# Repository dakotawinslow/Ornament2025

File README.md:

# Ornament2025
Repo of associated files for my Cristmas ornament 2025

See https://dakotawinslow.com for more details.

Shield: [![CC BY-SA 4.0][cc-by-sa-shield]][cc-by-sa]

This work is licensed under a
[Creative Commons Attribution-ShareAlike 4.0 International License][cc-by-sa].

[![CC BY-SA 4.0][cc-by-sa-image]][cc-by-sa]

[cc-by-sa]: http://creativecommons.org/licenses/by-sa/4.0/
[cc-by-sa-image]: https://licensebuttons.net/l/by-sa/4.0/88x31.png
[cc-by-sa-shield]: https://img.shields.io/badge/License-CC%20BY--SA%204.0-lightgrey.svg

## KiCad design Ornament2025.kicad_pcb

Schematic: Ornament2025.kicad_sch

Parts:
BT1: 3; BatteryHolder_uxcell_CR2450
C1, C2: 2.2uF; C_0805_2012Metric
D1, D2, D3: GRN; LED_D3.0mm
D4, D5, D6: RED; LED_D3.0mm
Q1, Q2: NPN; TO-92_Inline_Wide
R1, R2, R3: 6.8K; R_0805_2012Metric
R4, R5, R6: 1K; R_0805_2012Metric
R7, R9, R13, R14: 100K; R_0805_2012Metric
R8: 33K; R_0805_2012Metric
R10, R11: 18K; R_0805_2012Metric
R12, R16: 10K; R_0805_2012Metric
R15, R17, R18: 47K; R_0805_2012Metric
SW1, SW2, SW3: SW_SPST; PinHeader_1x03_P2.54mm_Vertical
U1: LMV358; SOIC-8-1EP_3.9x4.9mm_P1.27mm_EP2.29x3mm

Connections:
+1V5: C1.1, C2.1, R7.2, R12.2, R13.2, R16.1
+3V0: R1.1, R2.1, R3.1, R4.1, R5.1, R6.1, R12.1, SW1.2 (B), U1.8 (V+)
/Batt Positive: BT1.1 (+), SW1.1 (A)
/Green_Signal: R8.2, R9.2, R10.1, R17.2, U1.1
/Red_Signal: R11.1, R14.2, R15.2, R18.2, U1.7
GND: BT1.2 (-), Q1.1 (E), Q2.1 (E), R16.2, U1.4 (V-)
unnamed: D1.2 (A), R1.2
unnamed: D1.1 (K), D2.1 (K), D3.1 (K), Q1.3 (C)
unnamed: D2.2 (A), R2.2
unnamed: D3.2 (A), R3.2
unnamed: D4.2 (A), R4.2
unnamed: D4.1 (K), D5.1 (K), D6.1 (K), Q2.3 (C)
unnamed: D5.2 (A), R5.2
unnamed: D6.2 (A), R6.2
unnamed: Q1.2 (B), R10.2
unnamed: Q2.2 (B), R11.2
unnamed: C1.2, R9.1, SW2.1 (A), U1.2 (-)
unnamed: R17.1, SW2.2 (B)
unnamed: R18.1, SW3.1 (A)
unnamed: C2.2, R14.1, SW3.2 (B), U1.6 (-)
unnamed: R7.1, R8.1, U1.3 (+)
unnamed: R13.1, R15.1, U1.5 (+)

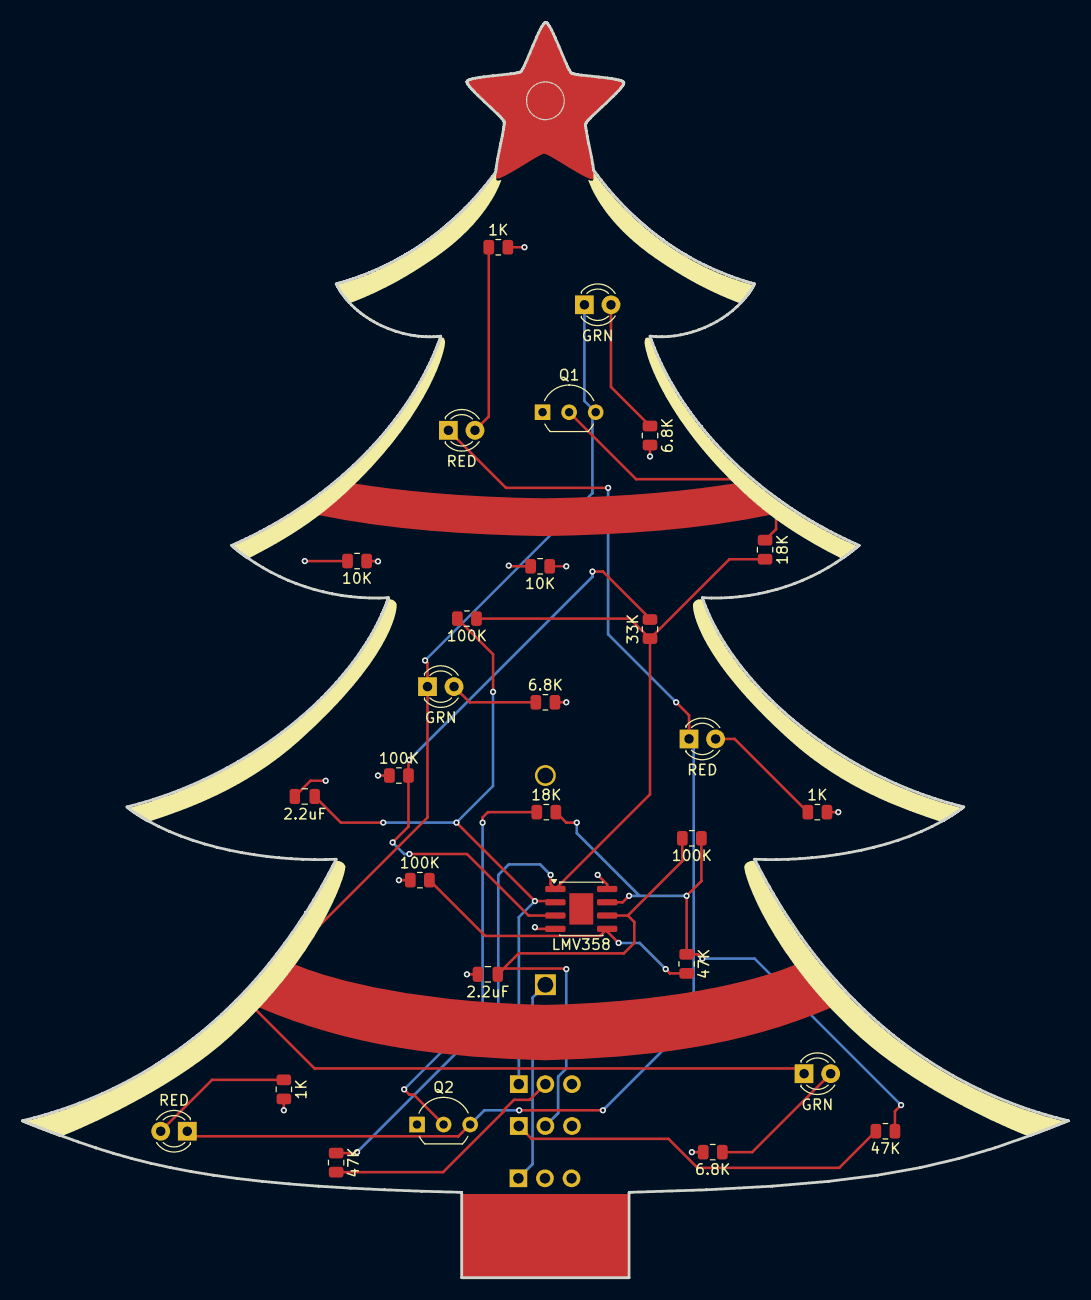
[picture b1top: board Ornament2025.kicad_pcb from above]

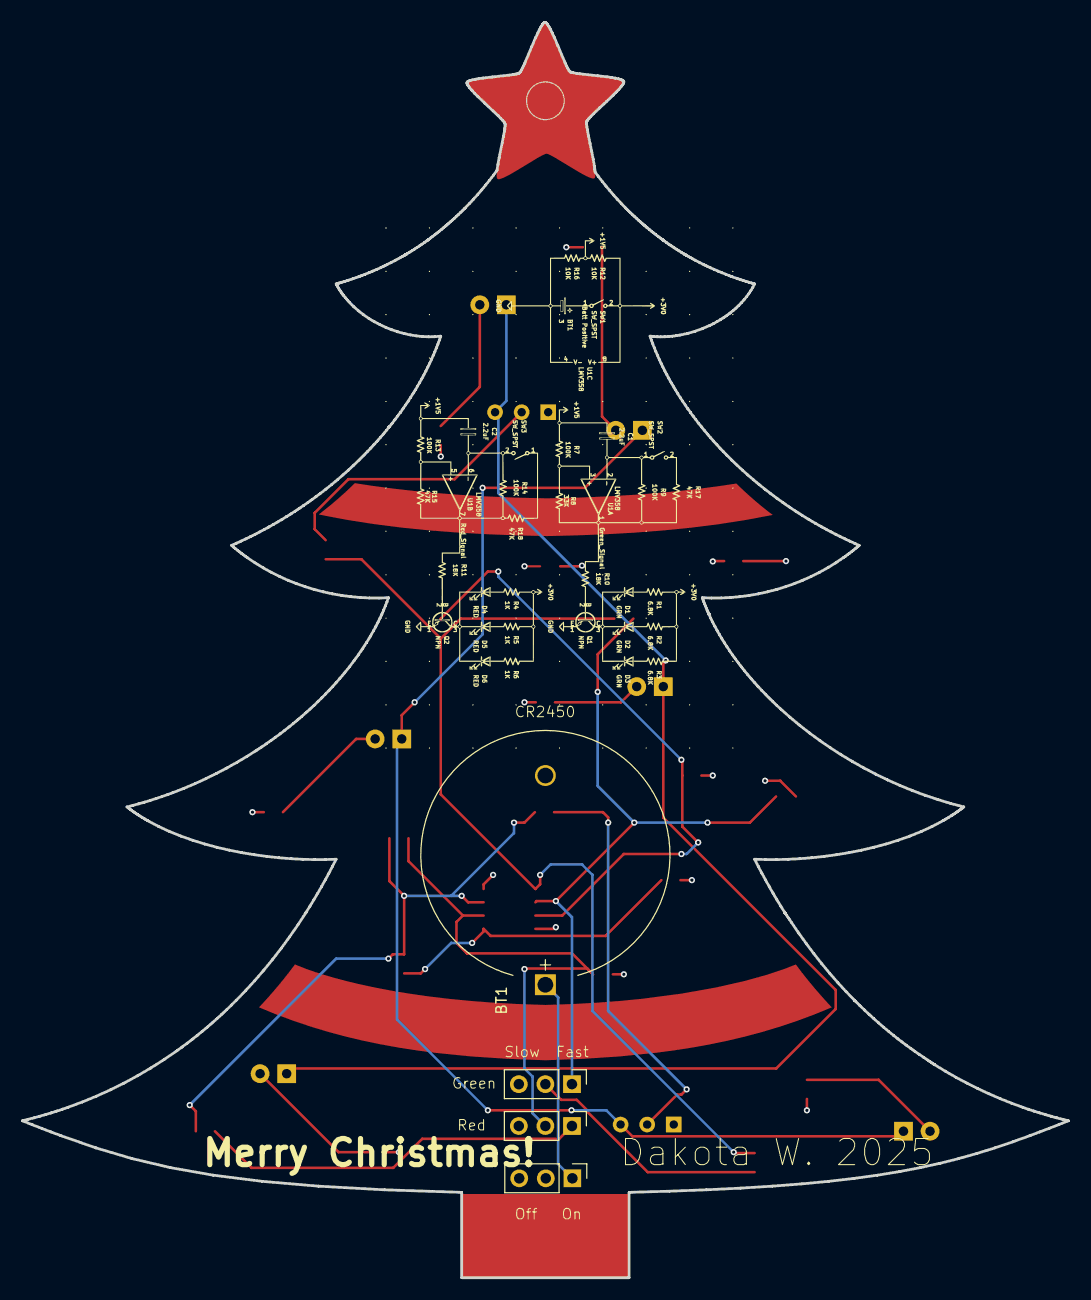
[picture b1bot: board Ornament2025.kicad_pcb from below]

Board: 4 copper layers, 100.0 x 120.0 mm, 33 parts (4 on the bottom side), 22 nets.

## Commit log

2026-01-20 Added License
2026-01-20 Add project details link to README
    Added a link for more details about the project.
